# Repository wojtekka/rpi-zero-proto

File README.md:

# Raspberry Pi Zero proto board

This is a simple proto board for Raspberry Pi Zero designed in [KiCAD](https://www.kicad-pcb.org/). This was my first project in KiCAD, so I probably didn't follow good practices. I did try to follow the [uHAT specification](https://github.com/raspberrypi/hats) though, so the board features a place for a TSSOP ID EEPROM. The pin description on silkscreen is probably smaller than the minimum of many PCB houses, but the $2 boards make by [JLCPCB](https://jlcpcb.com) turned out quite nice. All the signals are routed to pads below the connector to allow stacking pin headers, so there are only 7 rows of pins available for generic use. There are also two rows with power (3.3V and ground) on the side.

## License

The schematic and PCB layout are released into public domain. I'd love nothing more than to see it sold on [eBay](https://ebay.com) or [AliExpress](https://aliexpress.com) $0.99 for 5pcs.

The project uses modified KiCAD footprints licensed under CC-BY-SA 4.0.

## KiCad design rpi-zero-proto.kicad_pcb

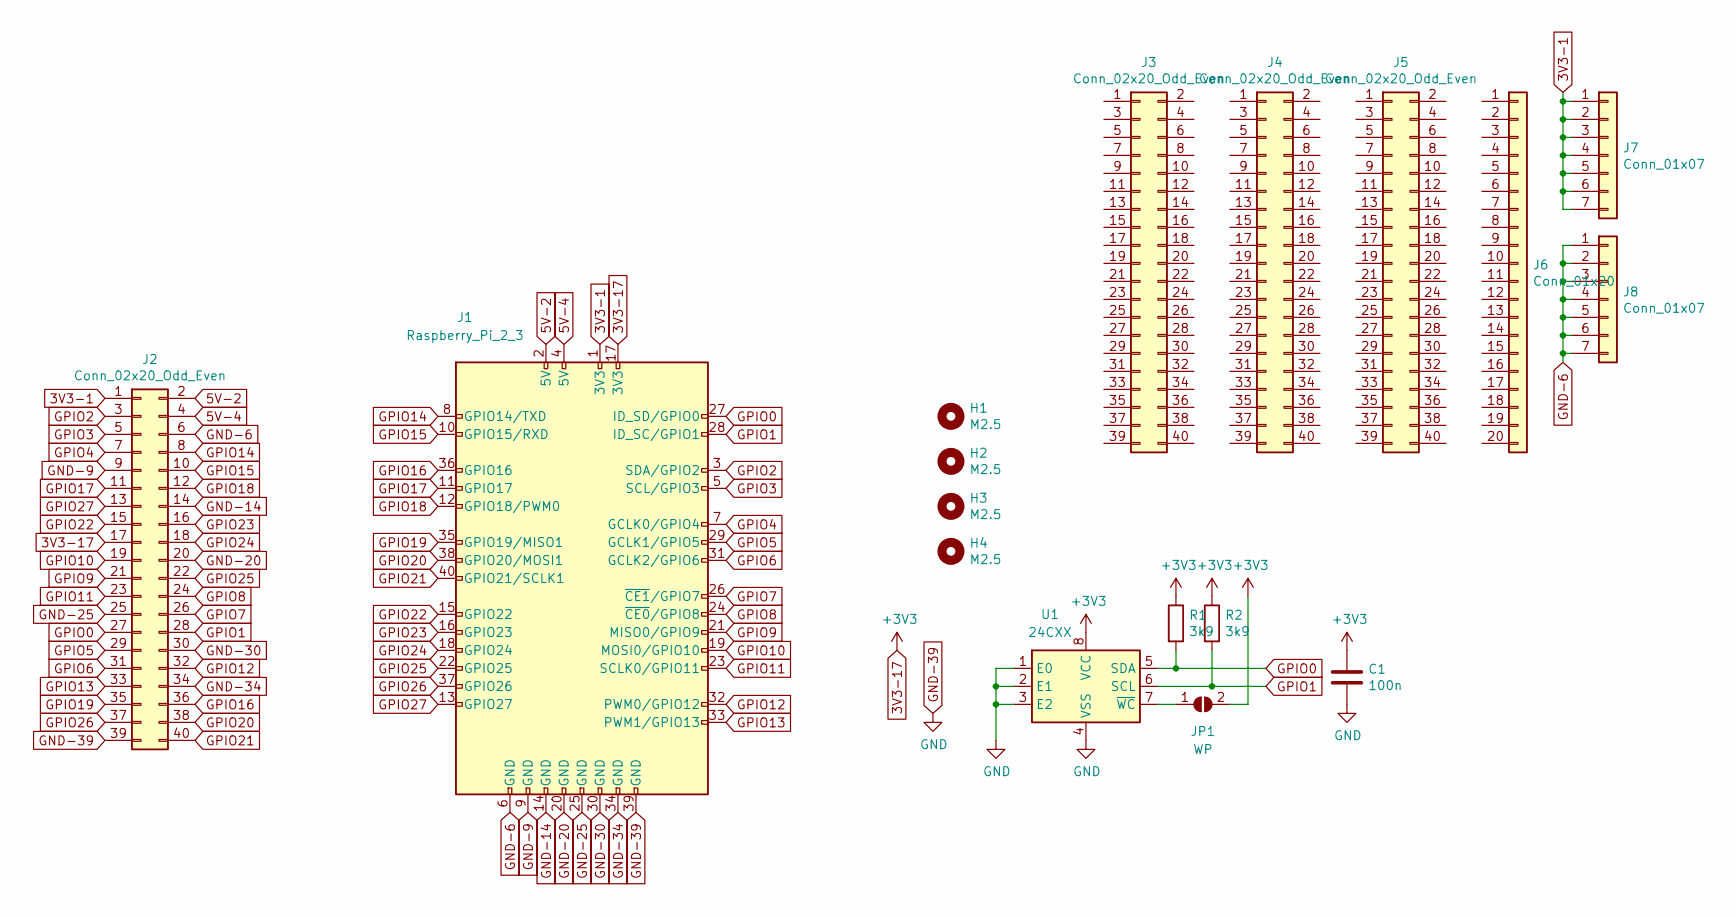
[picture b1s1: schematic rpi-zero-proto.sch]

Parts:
C1: 100n; C_0603_1608Metric
H1, H2, H3, H4: M2.5; MountingHole_2.5mm
J1: Raspberry_Pi_2_3; Pad_2x20_P2.54mm
J2, J3, J4, J5: Conn_02x20_Odd_Even; Pad_2x20_P2.54mm
J6: Conn_01x20; Pad_1x20_P2.54mm
J7, J8: Conn_01x07; Pad_1x07_P2.54mm
JP1: WP; SolderJumper-2_P1.3mm_Open_RoundedPad1.0x1.5mm
R1, R2: 3k9; R_0603_1608Metric
U1: 24CXX; TSSOP-8_4.4x3mm_P0.65mm

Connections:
3V3-1: J1.1 (3V3), J2.1, J7.1, J7.2, J7.3, J7.4, J7.5, J7.6, J7.7
3V3-17: C1.1, J1.17 (3V3), J2.17, JP1.2 (B), R1.1, R2.1, U1.8 (VCC)
5V-2: J1.2 (5V), J2.2
5V-4: J1.4 (5V), J2.4
GND-6: J1.6 (GND), J2.6, J8.1, J8.2, J8.3, J8.4, J8.5, J8.6, J8.7
GND-9: J1.9 (GND), J2.9
GND-14: J1.14 (GND), J2.14
GND-20: J1.20 (GND), J2.20
GND-25: J1.25 (GND), J2.25
GND-30: J1.30 (GND), J2.30
GND-34: J1.34 (GND), J2.34
GND-39: C1.2, J1.39 (GND), J2.39, U1.1 (E0), U1.2 (E1), U1.3 (E2), U1.4 (VSS)
GPIO0: J1.27 (ID_SD/GPIO0), J2.27, R1.2, U1.5 (SDA)
GPIO1: J1.28 (ID_SC/GPIO1), J2.28, R2.2, U1.6 (SCL)
GPIO2: J1.3 (SDA/GPIO2), J2.3
GPIO3: J1.5 (SCL/GPIO3), J2.5
GPIO4: J1.7 (GCLK0/GPIO4), J2.7
GPIO5: J1.29 (GCLK1/GPIO5), J2.29
GPIO6: J1.31 (GCLK2/GPIO6), J2.31
GPIO7: J1.26 (~CE1~/GPIO7), J2.26
GPIO8: J1.24 (~CE0~/GPIO8), J2.24
GPIO9: J1.21 (MISO0/GPIO9), J2.21
GPIO10: J1.19 (MOSI0/GPIO10), J2.19
GPIO11: J1.23 (SCLK0/GPIO11), J2.23
GPIO12: J1.32 (PWM0/GPIO12), J2.32
GPIO13: J1.33 (PWM1/GPIO13), J2.33
GPIO14: J1.8 (GPIO14/TXD), J2.8
GPIO15: J1.10 (GPIO15/RXD), J2.10
GPIO16: J1.36 (GPIO16), J2.36
GPIO17: J1.11 (GPIO17), J2.11
GPIO18: J1.12 (GPIO18/PWM0), J2.12
GPIO19: J1.35 (GPIO19/MISO1), J2.35
GPIO20: J1.38 (GPIO20/MOSI1), J2.38
GPIO21: J1.40 (GPIO21/SCLK1), J2.40
GPIO22: J1.15 (GPIO22), J2.15
GPIO23: J1.16 (GPIO23), J2.16
GPIO24: J1.18 (GPIO24), J2.18
GPIO25: J1.22 (GPIO25), J2.22
GPIO26: J1.37 (GPIO26), J2.37
GPIO27: J1.13 (GPIO27), J2.13
unnamed: JP1.1 (A), U1.7 (~WC)

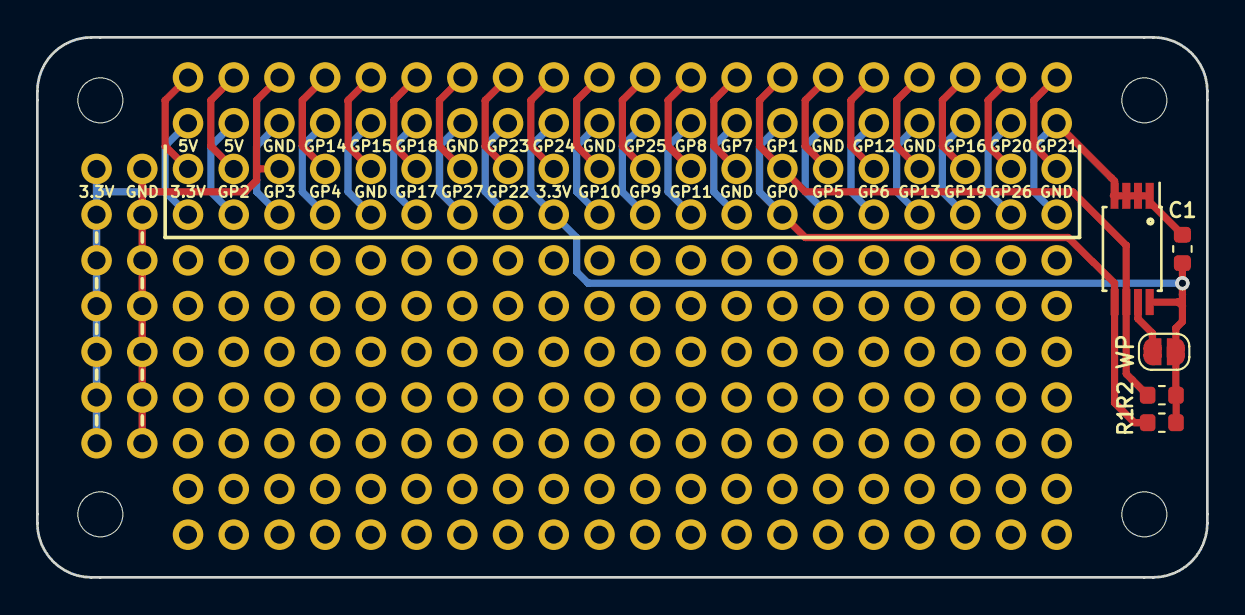
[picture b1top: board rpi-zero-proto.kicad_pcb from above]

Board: 2 copper layers, 65.0 x 30.0 mm, 17 parts (0 on the bottom side), 41 nets.

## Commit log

2019-12-10 One can dream.
